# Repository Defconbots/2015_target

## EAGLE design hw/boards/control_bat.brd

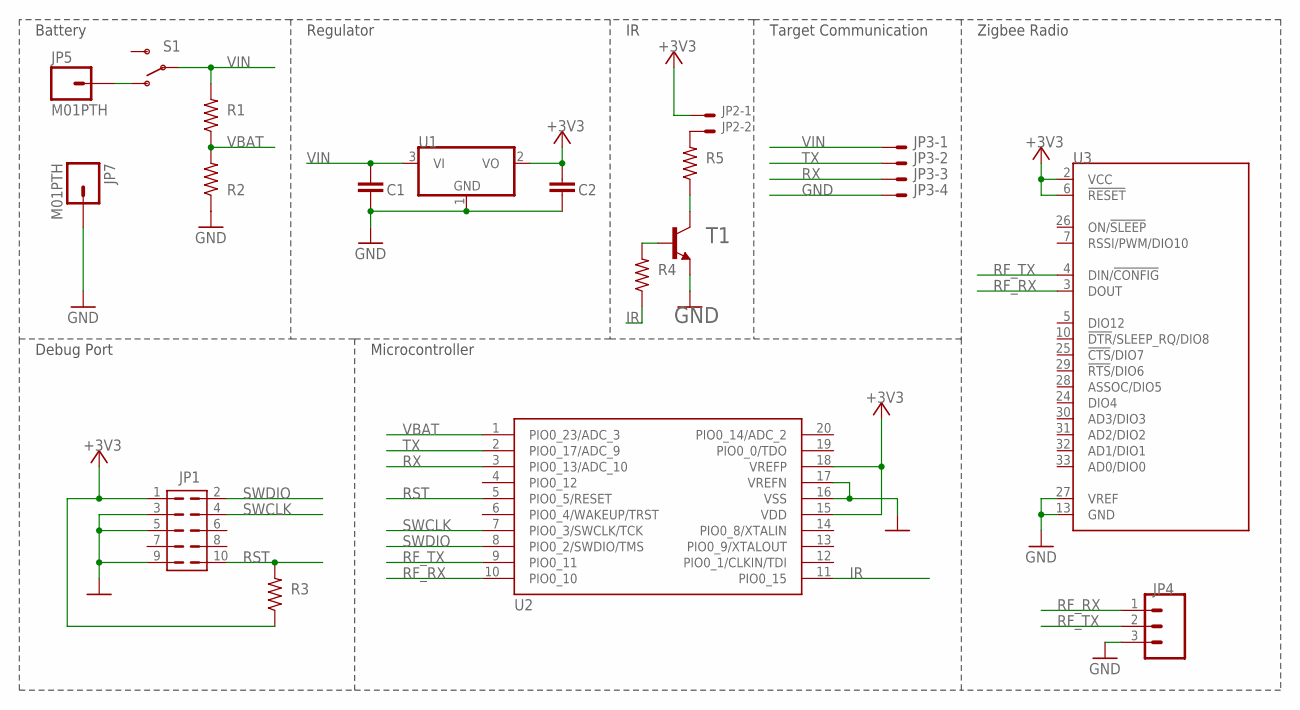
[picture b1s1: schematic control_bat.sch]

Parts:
C1, C2: C1608X5R1C106M080AB; 0603-CAP
JP1: FTSH-105-01-L; FTSH-105-01-XXX-DV-K
JP2: 798-DF132P125V20; 53398-02
JP3: 798-DF134P125V20; 53398-04
JP4: M03PTH; 1X03
JP5, JP7: M01PTH; 1X01
R1, R2, R3: 71-CRCW0603-10K-E3; R0603
R4: 71-CRCW0603220RFKEB; R0603
R5: 71-CRCW0603-5.6-E3; R0603
S1: 612-EG1270; EG1270
T1: PMBT4401,215; SOT23-BEC
U1: 579-MCP1703T-3002ECB; SOT23
U2: 771-LPC824M201JDH20J; TSSOP20
U3: 888-XB24CZ7PIS-004; XBEE-SMT

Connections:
+3V3: C2.1, JP1.1, JP2.1, R3.1, U1.2 (VO), U2.15 (VDD), U2.18 (VREFP), U3.2 (VCC), U3.6 (!RESET)
GND: C1.2, C2.2, JP1.3, JP1.5, JP1.9, JP3.4, JP4.3, JP7.1, R2.1, T1.E, U1.1 (GND), U2.16 (VSS), U2.17 (VREFN), U3.13 (GND), U3.27 (VREF)
IR: R4.1, U2.11 (PIO0_15)
unnamed: JP5.1, S1.P$1 (O)
unnamed: JP2.2, R5.2
unnamed: R5.1, T1.C
unnamed: R4.2, T1.B
RF_RX: JP4.1, U2.10 (PIO0_10), U3.3 (DOUT)
RF_TX: JP4.2, U2.9 (PIO0_11), U3.4 (DIN/!CONFIG)
RST: JP1.10, R3.2, U2.5 (PIO0_5/RESET)
RX: JP3.3, U2.3 (PIO0_13/ADC_10)
SWCLK: JP1.4, U2.7 (PIO0_3/SWCLK/TCK)
SWDIO: JP1.2, U2.8 (PIO0_2/SWDIO/TMS)
TX: JP3.2, U2.2 (PIO0_17/ADC_9)
VBAT: R1.1, R2.2, U2.1 (PIO0_23/ADC_3)
VIN: C1.1, JP3.1, R1.2, S1.P$2, U1.3 (VI)

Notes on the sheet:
Regulator
Microcontroller
Debug Port
Battery
Target Communication
Zigbee Radio

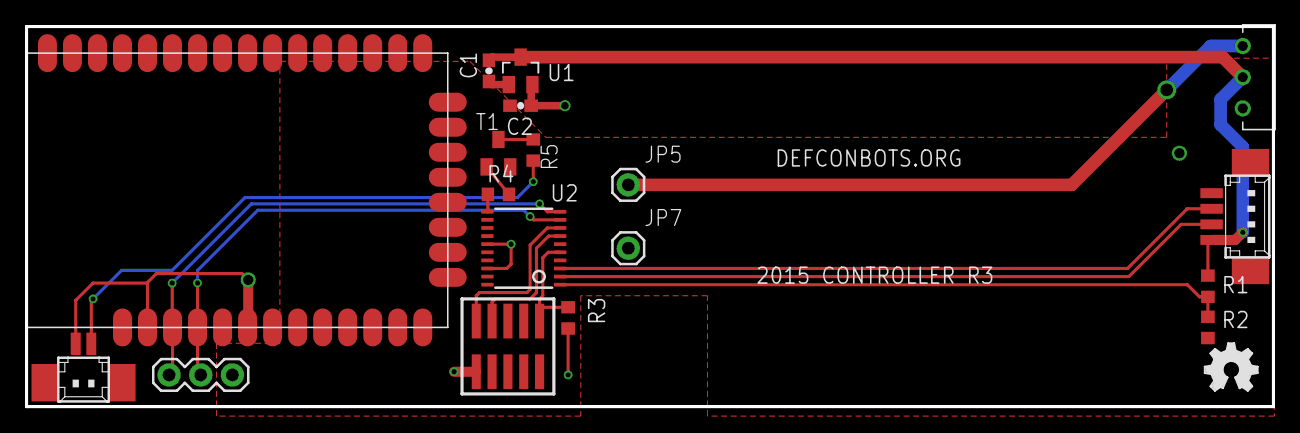
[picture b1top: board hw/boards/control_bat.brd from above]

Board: 2 copper layers, 100.0 x 30.5 mm, 19 parts (0 on the bottom side), 16 nets.

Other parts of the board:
LOGO1: OSHW_LOGO_FILLX0150-NT; OSHW_FILLX150_NOTEXT

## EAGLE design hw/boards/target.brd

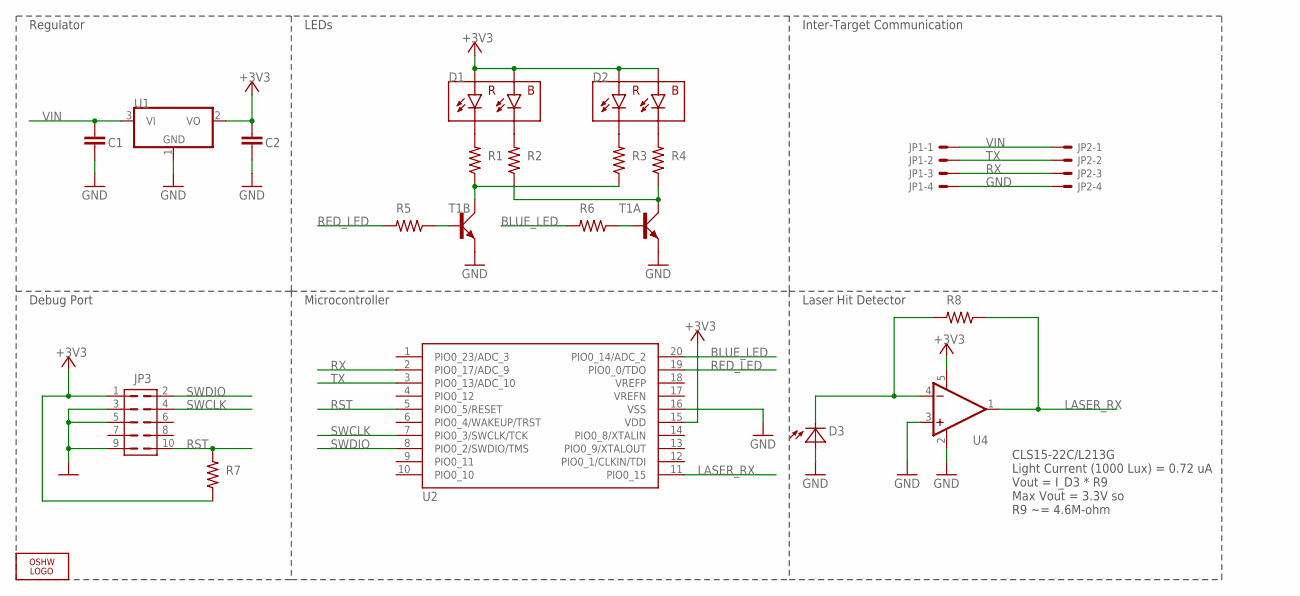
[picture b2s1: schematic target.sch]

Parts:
C1, C2: C1608X5R1C106M080AB; 0603-CAP
D1, D2: 150141RB73100; 150141RB
D3: 638-CLS1522CL213GTR8; CLS15
JP1, JP2: 798-DF134P125V20; 53398-04
JP3: FTSH-105-01-L; FTSH-105-01-XXX-DV-K
LOGO2: OSHW_LOGO_FILLX0150-NT; OSHW_FILLX150_NOTEXT
R1, R3: 71-CRCW060368R0FKEB; R0603
R2, R4: 71-CRCW0603-5.6-E3; R0603
R5, R6: 71-CRCW0603220RFKEB; R0603
R7: 71-CRCW0603-10K-E3; R0603
R8: 71-CRCW06034M64FKEA; R0603
T1: 771-BC847BS-T/R; SOT363_PHILIPS
U1: 579-MCP1703T-3002ECB; SOT23
U2: 771-LPC824M201JDH20J; TSSOP20
U4: 579-MCP6291T-E/OT; SOT23-5

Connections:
+3V3: C2.1, D1.1, D1.2, D2.1, D2.2, JP3.1, R7.1, U1.2 (VO), U2.15 (VDD), U4.5 (V+)
BLUE_LED: R6.2, U2.20 (PIO0_14/ADC_2)
GND: C1.2, C2.2, D3.1 (A), D3.2 (A), JP1.4, JP2.4, JP3.3, JP3.5, JP3.9, T1.1 (E), T1.4 (E), U1.1 (GND), U2.16 (VSS), U4.2 (V-), U4.3 (+IN)
LASER_RX: R8.1, U2.11 (PIO0_15), U4.1 (OUT)
unnamed: R2.1, R4.1, T1.6 (C)
unnamed: R1.1, R3.1, T1.3 (C)
unnamed: D1.3, R1.2
unnamed: R6.1, T1.2 (B)
unnamed: D3.3 (C), D3.4 (C), R8.2, U4.4 (-IN)
unnamed: D2.3, R3.2
unnamed: D1.4, R2.2
unnamed: D2.4, R4.2
unnamed: R5.1, T1.5 (B)
RED_LED: R5.2, U2.19 (PIO0_0/TDO)
RST: JP3.10, R7.2, U2.5 (PIO0_5/RESET)
RX: JP1.3, JP2.3, U2.2 (PIO0_17/ADC_9)
SWCLK: JP3.4, U2.7 (PIO0_3/SWCLK/TCK)
SWDIO: JP3.2, U2.8 (PIO0_2/SWDIO/TMS)
TX: JP1.2, JP2.2, U2.3 (PIO0_13/ADC_10)
VIN: C1.1, JP1.1, JP2.1, U1.3 (VI)

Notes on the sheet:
Regulator
LEDs
Inter-Target Communication
Microcontroller
Debug Port
Laser Hit Detector
CLS15-22C/L213G Light Current (1000 Lux) = 0.72 uA Vout = I_D3 * R9 Max Vout = 3.3V so R9 ~= 4.6M-ohm

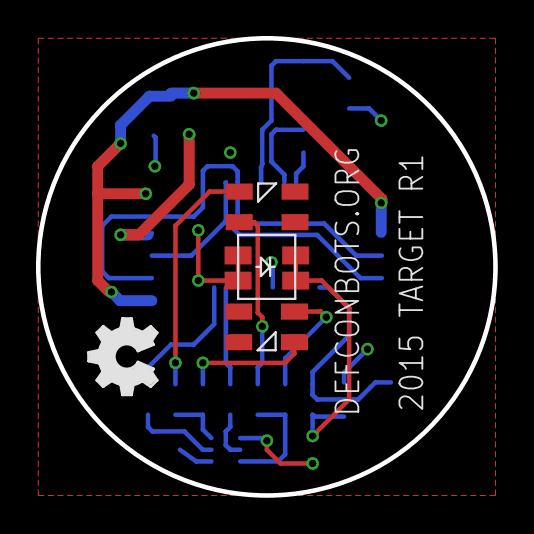
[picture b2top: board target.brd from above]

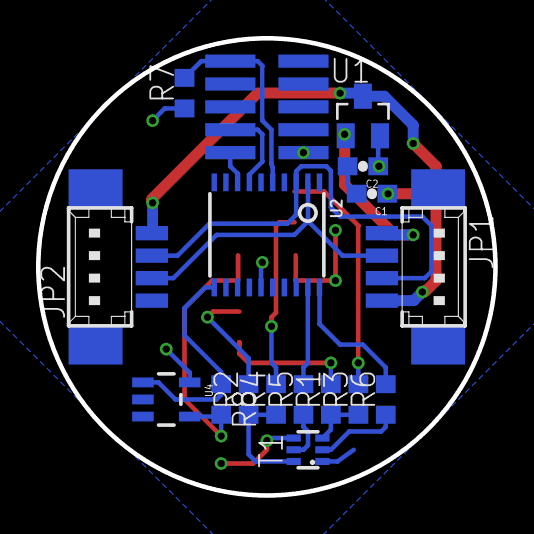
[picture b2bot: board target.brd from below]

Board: 2 copper layers, 25.4 x 25.4 mm, 21 parts (17 on the bottom side), 20 nets.

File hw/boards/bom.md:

## Control/Battery BOM

|Name            |Quantity|Part Number         |Distributor|
|:--------------:|:------:|:------------------:|:---------:|
|BAT1, BAT2, BAT3|3       |534-082             |Mouser     |
|U1              |1       |579-MCP1703T-3002ECB|Mouser     |
|S1              |1       |612-EG1270          |Mouser     |
|R1, R2, R3      |3       |71-CRCW0603-10K-E3  |Mouser     |
|R4              |1       |71-CRCW0603220RFKEB |Mouser     |
|U2              |1       |771-LPC824M201JDH20J|Mouser     |
|JP2             |1       |798-DF132P125V20    |Mouser     |
|JP3             |1       |798-DF134P125V20    |Mouser     |
|U3              |1       |888-XB24CZ7PIS-004  |Mouser     |
|C1, C2          |2       |C1608X5R1C106M080AB |Mouser     |
|JP1             |1       |FTSH-105-01-L       |Samtec     |

## Target BOM

|Name            |Quantity|Part Number         |Distributor|
|:--------------:|:------:|:------------------:|:---------:|
|D1, D2          |2       |150141RB73100       |Mouser     |
|U1              |1       |579-MCP1703T-3002ECB|Mouser     |
|U4              |1       |579-MCP6291T-E/OT   |Mouser     |
|D3              |1       |638-CLS1522CL213GTR8|Mouser     |
|R7              |1       |71-CRCW0603-10K-E3  |Mouser     |
|R2, R4          |2       |71-CRCW0603-5.6-E3  |Mouser     |
|R5, R6          |2       |71-CRCW0603220RFKEB |Mouser     |
|R8              |1       |71-CRCW06034M64FKEA |Mouser     |
|R1, R3          |2       |71-CRCW060368R0FKEB |Mouser     |
|T1              |1       |771-BC847BS-T/R     |Mouser     |
|U2              |1       |771-LPC824M201JDH20J|Mouser     |
|JP1, JP2        |2       |798-DF134P125V20    |Mouser     |
|C1, C2          |2       |C1608X5R1C106M080AB |Mouser     |
|JP3             |1       |M50-3600542         |Mouser     |

## Control/Target Interconnects

|Name            |Quantity|Part Number         |Distributor|
|:--------------:|:------:|:------------------:|:---------:|
|N/A             |1       |798-DF13-2S-1.25C   |Mouser     |
|N/A             |11      |798-DF13-4S-1.25C   |Mouser     |
|N/A             |30      |H4BBG-10110-B1-ND   |Digikey    |

## Misc Interface

|Name            |Quantity|Part Number         |Distributor|
|:--------------:|:------:|:------------------:|:---------:|
|N/A             |1       |602-1144-ND         |Digikey    |
|N/A             |1       |771-OM13071598      |Mouser     |

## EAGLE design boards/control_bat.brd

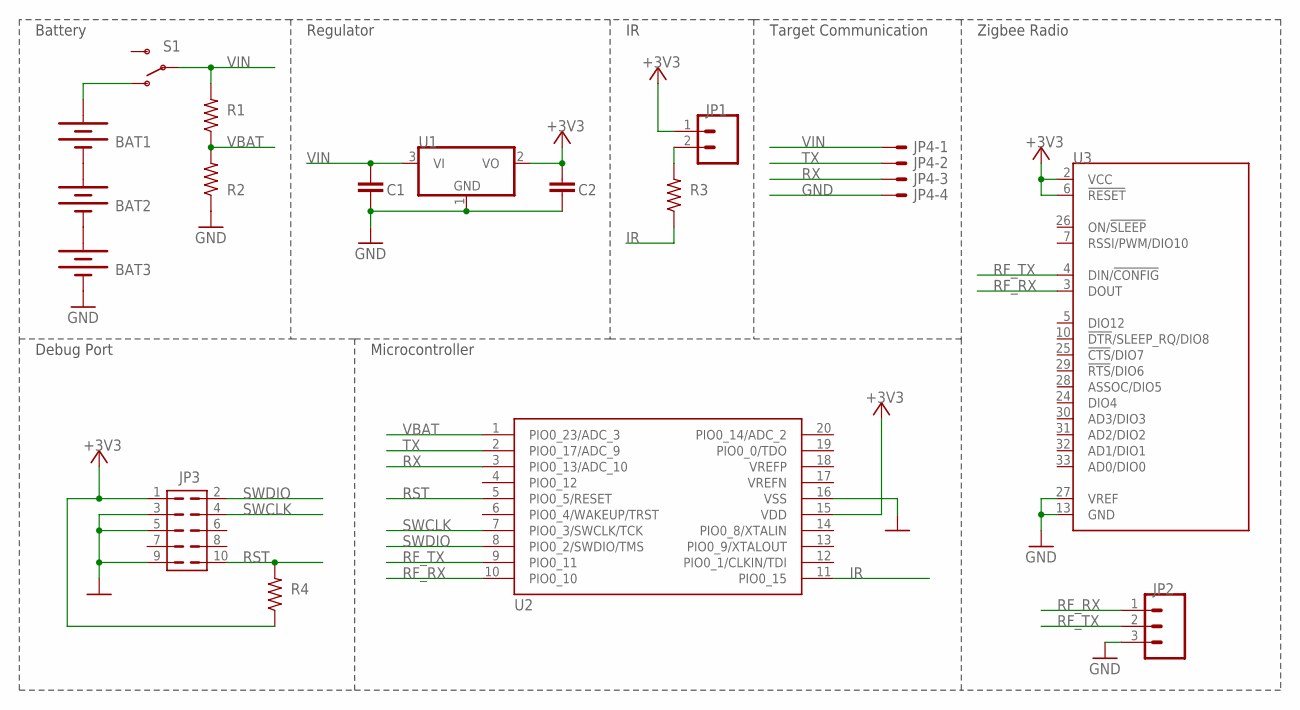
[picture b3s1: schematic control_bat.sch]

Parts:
BAT1, BAT2, BAT3: BATTERYAAA-KIT; BATTERY-AAA-KIT
C1, C2: C1608X5R1C106M080AB; 0603-CAP
JP1: M02PTH; 1X02
JP2: M03PTH; 1X03
JP3: FTSH-105-01-L; FTSH-105-01-XXX-DV-K
JP4: 798-DF134P125V20; 53398-04
R1, R2, R4: 71-CRCW0603-10K-E3; R0603
R3: 71-CRCW0603220RFKEB; R0603
S1: 612-EG1270; EG1270
U1: 579-MCP1703T-3002ECB; SOT23
U2: 771-LPC824M201JDH20J; TSSOP20
U3: 888-XB24CZ7PIS-004; XBEE-SMT

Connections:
+3V3: C2.1, JP1.1, JP3.1, R4.1, U1.2 (VO), U2.15 (VDD), U3.2 (VCC), U3.6 (!RESET)
GND: BAT3.GND@1 (-), C1.2, C2.2, JP2.3, JP3.3, JP3.5, JP3.9, JP4.4, R2.1, U1.1 (GND), U2.16 (VSS), U3.13 (GND), U3.27 (VREF)
IR: R3.1, U2.11 (PIO0_15)
unnamed: BAT2.GND@1 (-), BAT3.PWR@1 (+)
unnamed: BAT1.GND@1 (-), BAT2.PWR@1 (+)
unnamed: BAT1.PWR@1 (+), S1.P$1 (O)
unnamed: JP1.2, R3.2
RF_RX: JP2.1, U2.10 (PIO0_10), U3.3 (DOUT)
RF_TX: JP2.2, U2.9 (PIO0_11), U3.4 (DIN/!CONFIG)
RST: JP3.10, R4.2, U2.5 (PIO0_5/RESET)
RX: JP4.3, U2.3 (PIO0_13/ADC_10)
SWCLK: JP3.4, U2.7 (PIO0_3/SWCLK/TCK)
SWDIO: JP3.2, U2.8 (PIO0_2/SWDIO/TMS)
TX: JP4.2, U2.2 (PIO0_17/ADC_9)
VBAT: R1.1, R2.2, U2.1 (PIO0_23/ADC_3)
VIN: C1.1, JP4.1, R1.2, S1.P$2, U1.3 (VI)

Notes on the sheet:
Regulator
Microcontroller
Debug Port
Battery
Target Communication
Zigbee Radio

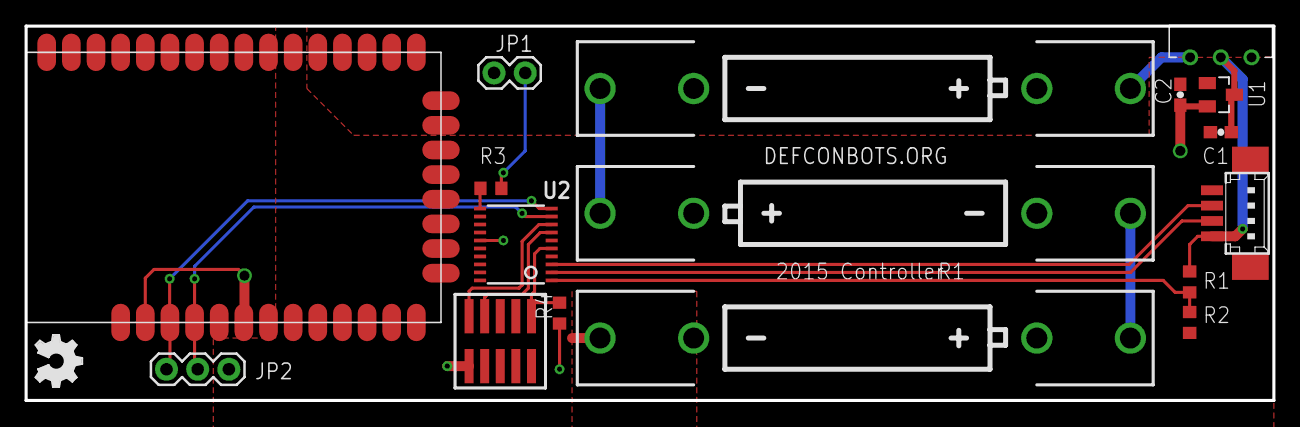
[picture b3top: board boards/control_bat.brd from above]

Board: 2 copper layers, 101.6 x 30.5 mm, 18 parts (0 on the bottom side), 16 nets.

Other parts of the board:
LOGO1: OSHW_LOGO_FILLX0150-NT; OSHW_FILLX150_NOTEXT

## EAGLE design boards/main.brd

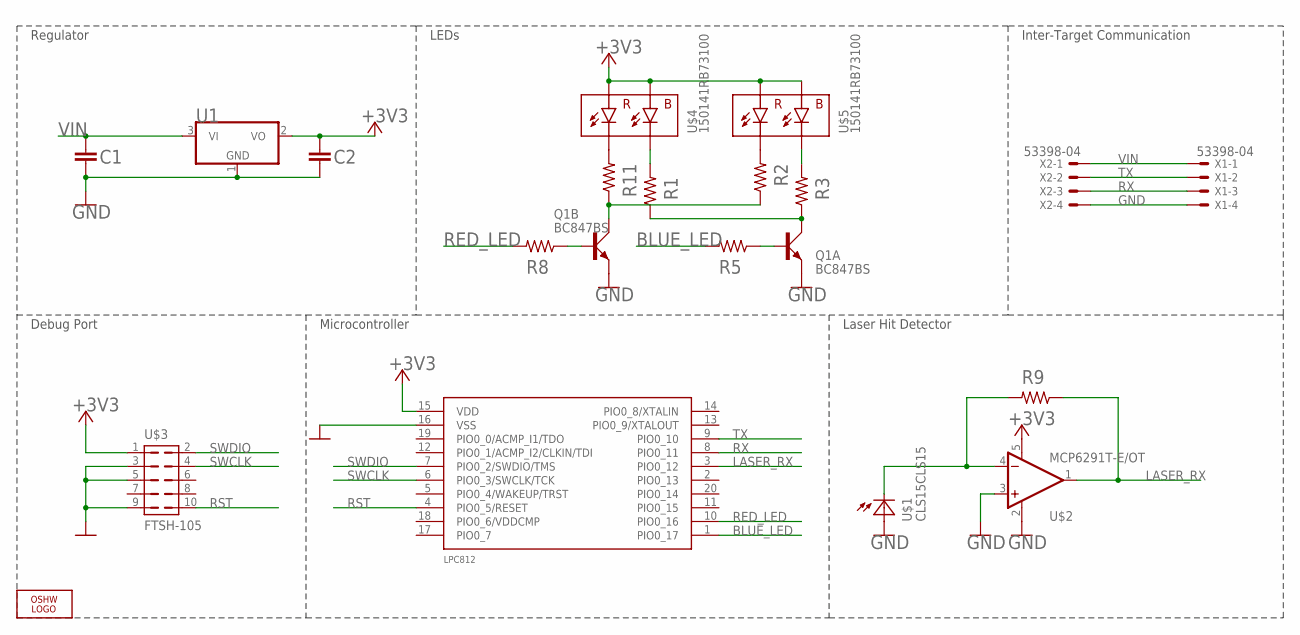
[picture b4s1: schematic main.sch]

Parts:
C1, C2: C1608X5R1C106M080AB; 0603-CAP
LOGO2: OSHW_LOGO_FILLX0150-NT; OSHW_FILLX150_NOTEXT
LPC812: LPC812M101JDH20; TSSOP20
Q1: BC847BS; SOT363_PHILIPS
R1, R2, R3, R5, R8, R9, R11: CRCW0603200RFKEA; R0603
U1: MCP1703T-3002E/CB; SOT23
U$1: CLS15CLS15; CLS15
U$2: MCP6291T-E/OT; SOT23-5
U$3: FTSH-105; FTSH-105-01-XXX-DV-K
U$4, U$5: 150141RB73100; 150141RB
X1, X2: 53398-04

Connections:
+3V3: C2.1, LPC812.15 (VDD), U1.2 (VO), U$2.5 (V+), U$3.1, U$4.1, U$4.2, U$5.1, U$5.2
BLUE_LED: LPC812.1 (PIO0_17), R5.2
GND: C1.2, C2.2, LPC812.16 (VSS), Q1.1 (E), Q1.4 (E), U1.1 (GND), U$1.1 (A), U$1.2 (A), U$2.2 (V-), U$2.3 (+IN), U$3.3, U$3.5, U$3.9, X1.4, X2.4
LASER_RX: LPC812.3 (PIO0_12), R9.1, U$2.1 (OUT)
unnamed: Q1.6 (C), R1.1, R3.1
unnamed: Q1.3 (C), R2.1, R11.1
unnamed: R11.2, U$4.3
unnamed: Q1.2 (B), R5.1
unnamed: R9.2, U$1.3 (C), U$1.4 (C), U$2.4 (-IN)
unnamed: R2.2, U$5.3
unnamed: R1.2, U$4.4
unnamed: R3.2, U$5.4
unnamed: Q1.5 (B), R8.1
RED_LED: LPC812.10 (PIO0_16), R8.2
RST: LPC812.4 (PIO0_5/RESET), U$3.10
RX: LPC812.8 (PIO0_11), X1.3, X2.3
SWCLK: LPC812.6 (PIO0_3/SWCLK/TCK), U$3.4
SWDIO: LPC812.7 (PIO0_2/SWDIO/TMS), U$3.2
TX: LPC812.9 (PIO0_10), X1.2, X2.2
VIN: C1.1, U1.3 (VI), X1.1, X2.1

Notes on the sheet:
Regulator
LEDs
Inter-Target Communication
Microcontroller
Debug Port
Laser Hit Detector

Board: 2 copper layers, 20 parts (16 on the bottom side), 20 nets, no tracks yet.

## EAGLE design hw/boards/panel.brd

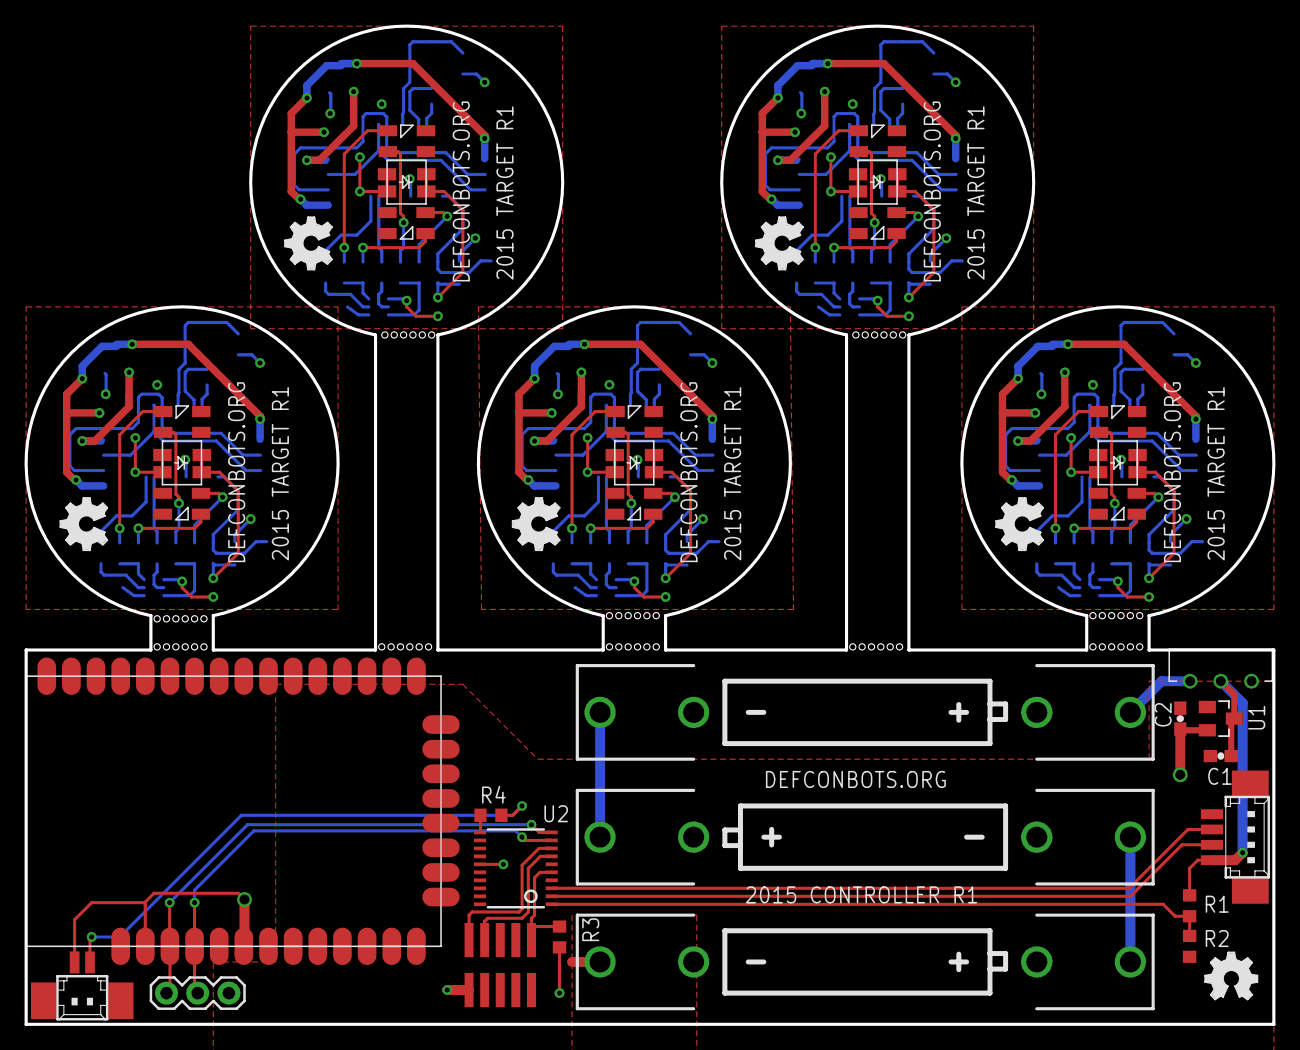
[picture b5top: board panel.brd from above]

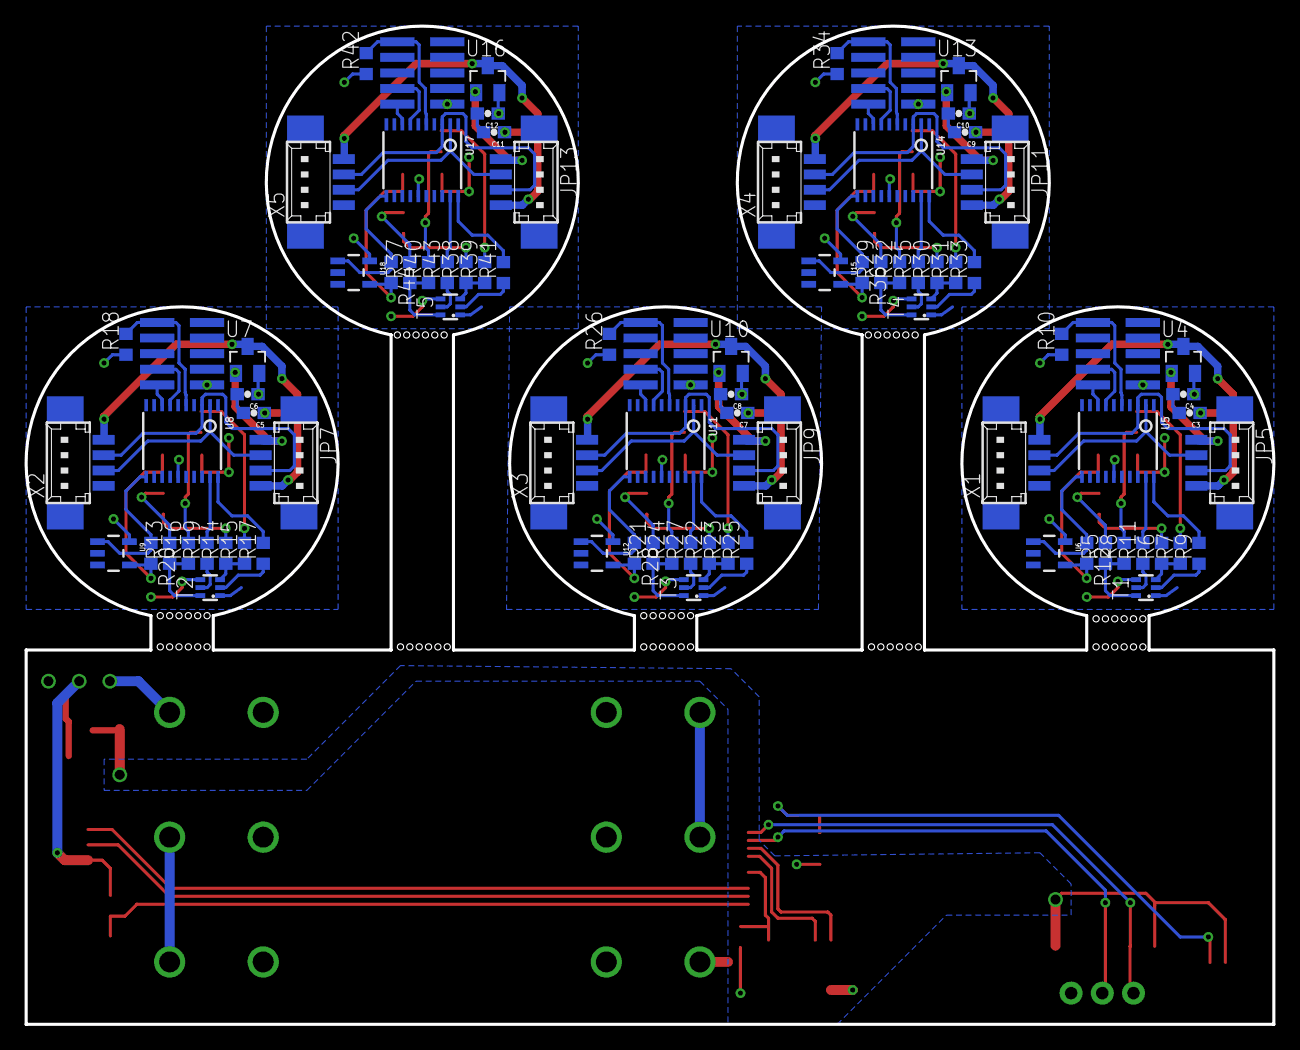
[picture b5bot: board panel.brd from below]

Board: 2 copper layers, 101.6 x 81.3 mm, 123 parts (85 on the bottom side), 116 nets.

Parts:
BAT1, BAT2, BAT3: 534-082; BATTERY-AAA-KIT
C1, C2, C3, C4, C5, C6, C7, C8, C9, C10, C11, C12: C1608X5R1C106M080AB; 0603-CAP
D1, D2, D4, D5, D7, D8, D10, D11, D13, D14: 150141RB73100; 150141RB
D3, D6, D9, D12, D15: 638-CLS1522CL213GTR8; CLS15
JP1, JP6, JP8, JP10, JP12, JP14: FTSH-105-01-L; FTSH-105-01-XXX-DV-K
JP2: 798-DF132P125V20; 53398-02
JP3, JP5, JP7, JP9, JP11, JP13: 798-DF134P125V20; 53398-04
JP4: 1X03
LOGO1, LOGO2, LOGO3, LOGO4, LOGO5, LOGO6: OSHW_LOGO_FILLX0150-NT; OSHW_FILLX150_NOTEXT
R1, R2, R3, R10, R18, R26, R34, R42: 71-CRCW0603-10K-E3; R0603
R4, R9, R11, R17, R19, R25, R27, R33, R35, R41, R43: 71-CRCW0603220RFKEB; R0603
R5, R8, R13, R16, R21, R24, R29, R32, R37, R40: 71-CRCW0603-5.6-E3; R0603
R6, R7, R14, R15, R22, R23, R30, R31, R38, R39: 71-CRCW060368R0FKEB; R0603
R12, R20, R28, R36, R44: 71-CRCW06034M64FKEA; R0603
S1: 612-EG1270; EG1270
T1, T2, T3, T4, T5: 771-BC847BS-T/R; SOT363_PHILIPS
U1, U4, U7, U10, U13, U16: 579-MCP1703T-3002ECB; SOT23
U2, U5, U8, U11, U14, U17: 771-LPC824M201JDH20J; TSSOP20
U3: 888-XB24CZ7PIS-004; XBEE-SMT
U6, U9, U12, U15, U18: 579-MCP6291T-E/OT; SOT23-5
X1, X2, X3, X4, X5: 798-DF134P125V20; 53398-04

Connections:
+3V1: C4.1, D1.1, D1.2, D2.1, D2.2, JP6.1, R10.1, U4.2, U5.15, U6.5
+3V2: C6.1, D4.1, D4.2, D5.1, D5.2, JP8.1, R18.1, U7.2, U8.15, U9.5
+3V3: C2.1, JP1.1, JP2.1, R3.1, U1.2, U2.15, U3.2, U3.6
+3V4: C8.1, D7.1, D7.2, D8.1, D8.2, JP10.1, R26.1, U10.2, U11.15, U12.5
+3V5: C10.1, D10.1, D10.2, D11.1, D11.2, JP12.1, R34.1, U13.2, U14.15, U15.5
+3V6: C12.1, D13.1, D13.2, D14.1, D14.2, JP14.1, R42.1, U16.2, U17.15, U18.5
BLUE_LED: R9.2, U5.20
BLUE_LED1: R17.2, U8.20
BLUE_LED2: R25.2, U11.20
BLUE_LED3: R33.2, U14.20
BLUE_LED4: R41.2, U17.20
GND: BAT3.GND@1, C1.2, C2.2, JP1.3, JP1.5, JP1.9, JP3.4, JP4.3, R2.1, U1.1, U2.16, U3.13, U3.27
GND1: C3.2, C4.2, D3.1, D3.2, JP5.4, JP6.3, JP6.5, JP6.9, T1.1, T1.4, U4.1, U5.16, U6.2, U6.3, X1.4
GND2: C5.2, C6.2, D6.1, D6.2, JP7.4, JP8.3, JP8.5, JP8.9, T2.1, T2.4, U7.1, U8.16, U9.2, U9.3, X2.4
GND3: C7.2, C8.2, D9.1, D9.2, JP9.4, JP10.3, JP10.5, JP10.9, T3.1, T3.4, U10.1, U11.16, U12.2, U12.3, X3.4
GND4: C9.2, C10.2, D12.1, D12.2, JP11.4, JP12.3, JP12.5, JP12.9, T4.1, T4.4, U13.1, U14.16, U15.2, U15.3, X4.4
GND5: C11.2, C12.2, D15.1, D15.2, JP13.4, JP14.3, JP14.5, JP14.9, T5.1, T5.4, U16.1, U17.16, U18.2, U18.3, X5.4
IR: R4.1, U2.11
LASER_RX: R12.1, U5.11, U6.1
LASER_RX1: R20.1, U8.11, U9.1
LASER_RX2: R28.1, U11.11, U12.1
LASER_RX3: R36.1, U14.11, U15.1
LASER_RX4: R44.1, U17.11, U18.1
unnamed: BAT2.GND@1, BAT3.PWR@1
unnamed: BAT1.GND@1, BAT2.PWR@1
unnamed: BAT1.PWR@1, S1.P$1
unnamed: JP2.2, R4.2
unnamed: D3.3, D3.4, R12.2, U6.4
unnamed: R9.1, T1.2
unnamed: R6.1, R7.1, T1.3
unnamed: D1.3, R6.2
unnamed: D2.3, R7.2
unnamed: D1.4, R5.2
unnamed: R11.1, T1.5
unnamed: D2.4, R8.2
unnamed: R5.1, R8.1, T1.6
unnamed: D6.3, D6.4, R20.2, U9.4
unnamed: R17.1, T2.2
unnamed: R19.1, T2.5
unnamed: R14.1, R15.1, T2.3
unnamed: D4.3, R14.2
unnamed: D5.3, R15.2
unnamed: D4.4, R13.2
unnamed: D5.4, R16.2
unnamed: R13.1, R16.1, T2.6
unnamed: D9.3, D9.4, R28.2, U12.4
unnamed: R25.1, T3.2
unnamed: R27.1, T3.5
unnamed: R22.1, R23.1, T3.3
unnamed: D7.3, R22.2
unnamed: D8.3, R23.2
unnamed: D7.4, R21.2
unnamed: D8.4, R24.2
unnamed: R21.1, R24.1, T3.6
unnamed: D12.3, D12.4, R36.2, U15.4
unnamed: R33.1, T4.2
unnamed: R35.1, T4.5
unnamed: R30.1, R31.1, T4.3
unnamed: D10.3, R30.2
unnamed: D11.3, R31.2
unnamed: D10.4, R29.2
unnamed: D11.4, R32.2
unnamed: R29.1, R32.1, T4.6
unnamed: D15.3, D15.4, R44.2, U18.4
unnamed: R41.1, T5.2
unnamed: R43.1, T5.5
unnamed: R38.1, R39.1, T5.3
unnamed: D13.3, R38.2
unnamed: D14.3, R39.2
unnamed: D13.4, R37.2
unnamed: D14.4, R40.2
unnamed: R37.1, R40.1, T5.6
RED_LED: R11.2, U5.19
RED_LED1: R19.2, U8.19
RED_LED2: R27.2, U11.19
RED_LED3: R35.2, U14.19
RED_LED4: R43.2, U17.19
RF_RX: JP4.1, U2.10, U3.3
RF_TX: JP4.2, U2.9, U3.4
RST: JP1.10, R3.2, U2.5
RST1: JP6.10, R10.2, U5.5
RST2: JP8.10, R18.2, U8.5
RST3: JP10.10, R26.2, U11.5
RST4: JP12.10, R34.2, U14.5
RST5: JP14.10, R42.2, U17.5
RX: JP3.3, U2.3
RX1: JP5.3, U5.2, X1.3
RX2: JP7.3, U8.2, X2.3
RX3: JP9.3, U11.2, X3.3
RX4: JP11.3, U14.2, X4.3
RX5: JP13.3, U17.2, X5.3
SWCLK: JP1.4, U2.7
SWCLK1: JP6.4, U5.7
SWCLK2: JP8.4, U8.7
SWCLK3: JP10.4, U11.7
SWCLK4: JP12.4, U14.7
SWCLK5: JP14.4, U17.7
SWDIO: JP1.2, U2.8
SWDIO1: JP6.2, U5.8
SWDIO2: JP8.2, U8.8
SWDIO3: JP10.2, U11.8
SWDIO4: JP12.2, U14.8
SWDIO5: JP14.2, U17.8
TX: JP3.2, U2.2
TX1: JP5.2, U5.3, X1.2
TX2: JP7.2, U8.3, X2.2
TX3: JP9.2, U11.3, X3.2
TX4: JP11.2, U14.3, X4.2
TX5: JP13.2, U17.3, X5.2
VBAT: R1.1, R2.2, U2.1
VIN: C1.1, JP3.1, R1.2, S1.P$2, U1.3
VIN1: C3.1, JP5.1, U4.3, X1.1
VIN2: C5.1, JP7.1, U7.3, X2.1
VIN3: C7.1, JP9.1, U10.3, X3.1
VIN4: C9.1, JP11.1, U13.3, X4.1
VIN5: C11.1, JP13.1, U16.3, X5.1

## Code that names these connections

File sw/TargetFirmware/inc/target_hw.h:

#ifndef TARGET_HW_H
#define TARGET_HW_H

#define IO_HIGH(p)   Chip_GPIO_SetPinOutHigh(LPC_GPIO_PORT,0,p)
#define IO_LOW(p)    Chip_GPIO_SetPinOutLow(LPC_GPIO_PORT,0,p)
#define IO_TOGGLE(p) Chip_GPIO_SetPinToggle(LPC_GPIO_PORT,0,p)
#define IO_READ(p)   Chip_GPIO_GetPinState(LPC_GPIO_PORT,0,p)
#define IO_OUTPUT(p) Chip_GPIO_SetPinDIROutput(LPC_GPIO_PORT,0,p)
#define IO_INPUT(p)  Chip_GPIO_SetPinDIRInput(LPC_GPIO_PORT,0,p)

static const uint8_t pin_rx        = 17;
static const uint8_t pin_tx        = 13;
static const uint8_t pin_tx_idle   = 10;
static const uint8_t pin_blue_led  = 14;
static const uint8_t pin_blue_idle = 23;
static const uint8_t pin_red_led   = 0;
static const uint8_t pin_red_idle  = 12;
static const uint8_t pin_laser_rx = 15;

#endif

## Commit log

2014-11-04 A start.
2014-11-05 Rough schematic, aproximate placement.
2014-11-07 Swap msp430 for LPC8* arm processor. Add battery/controller-radio board
2014-11-08 First pass layout of control/battery board
2014-11-08 Add serial debug port on xbee in case I need to configure it manually
2014-11-08 Some ground plane improvements
2014-11-08 Fix footprint (was footprint for LPC812 instead of LPC824). Update part numbers on the schematic. Add IR. Cleanup ground plane.
2014-11-08 Probably not a bad idea to have a pullup on the reset line.
2014-11-08 Add a junction...
2014-11-08 Rename to target.sch/brd. Fix controller. Add part numbers. Still needs to be routed.
2014-11-08 Fix overlap
2014-11-09 Working on target layout
2014-11-09 First pass target route
2014-11-23 Add start of TargetControl app
2014-11-24 Cleanup some routing. Fix some part numbers
2014-11-24 Cleanup some parts, generate BOM.
2014-11-24 Panelize the boards for fab
2014-11-24 Fix some part numbers
2014-11-24 Fix fonts
2014-11-24 Panel was missing some holes for breakoff
2014-11-24 Gerbers from the panel.
2014-11-24 Remove output binaries from source control
2014-11-24 Switch to use Caliburn micro MVVM
2014-11-24 Fix teams in initial startup
2014-11-25 Get rid of the panel, prep for proto order with dirty PCBs.
2014-11-25 fix silkscreen
2014-11-25 Fix length to be 10cm
2014-11-25 Fix silkscreen. again.
2014-11-25 Add individual gerbers.
2014-11-27 Clean up/add some docs.
2014-11-28 Add shell of firmware project.
2014-11-28 Add interconnect/interface stuff.
2014-12-01 Add more up-to-date example code.
2014-12-01 Move sci spec into repo.
2014-12-01 Update driver lib to LPCopen 2.03. Structure initial target controller.
    I don't have hardware so nothing is tested at this point. Just laying the groundwork for the eventual application.
2014-12-02 Fill in all the sci functions. Add target framework.
2014-12-03 Fix some casts. Make target only respond to '*' address from the laser.
2014-12-03 Axe the read/write-only errors.
2014-12-03 Add the xstick driver so no one has to go looking for it.
2014-12-09 Remote target control app(now in it's own repo)
2014-12-09 Add license
2014-12-11 This doesn't belong.
2014-12-11 General cleanup. RF tx/rx tested.
2014-12-16 Fix adc.
    There is no internal reference so I needed to connect the VREFP/VREFN pints to VCC/GND. Added init code to read single adc samples when the voltage-read command is passed.
2014-12-18 Working on the train IR reverse engineering. PWM works but not the actual signaling.
2014-12-19 Fix schedule tick time to be 1ms. This also fixed the train speed signaling.
2015-01-25 All commands are up and running but the RX from targets is erratic, possibly due to noise.
    Here are a few major findings:
    - There is an interaction between the ADC and the RX line on the controller board. I fixed it by disabling the ADC pin when not in use but needed to add an enable-delay-disable in the voltage-read fu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
    - The tx/rx on the target board is swapped so I swapped it in the uart init.
    - The uart speed was changed from 115k to 56k, but it hasn't seem to make the link more reliable -- will possibly change it back in the future.
2015-01-25 Fix ADC sequency from killing the serial RX.
    For some reason when the ADC sequencer is running it killed the rx port. Initially I thought rx performance was erratic but it turns out after any ADC reading it would stop working. Fixed by disablin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
2015-05-12 Some updates to try and get the bus-tx to work.
2015-05-13 Fix tx bus problem.
    All targets share the same tx-rx lines. The RX lines float but, by default, the TX line has an internal pull-up. Whenever more than 2 targets were attached the logic-voltage of the tx line would only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
2015-06-14 Update SCI to add address and device data to responses. Update SCI access accordingly. Fix bug where stop byte of response packets was incorrect because we weren't waiting long enough after a transmi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
2015-06-29 Add address info to errors.
2015-06-30 Fix wording...
2015-07-05 Add address to error response and make LEDs turn off all the way when you set brightness to 0.
2015-07-26 Ir LED handling not PWM anymore. Now constantly sends.
2015-07-26 Fix issue with targets not releasing the tx line on the bus occasionally.
2015-07-26 How are you gentlemen?
2015-07-29 Switch ir pin back to PWM.
    So I originally used a scope and reverse engineered the IR protocol noting a 40khz carrier freq. Months later, when I was debugging the code, I didn't have a scope and used a logic analyzer instead, 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
2015-07-31 Final fixes to the controller board.
    This board will probably never be fabbed but I'm documenting the fixes made to hardware here for future reference.

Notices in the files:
parts and their libraries:
SparkFun-Passives: Licensing: CC v3.0 Share-Alike You are welcome to use this library for commercial purposes.
SparkFun-Electromechanical: Licensing: Creative Commons ShareAlike 4.0 International - https://creativecommons.org/licenses/by-sa/4.0
